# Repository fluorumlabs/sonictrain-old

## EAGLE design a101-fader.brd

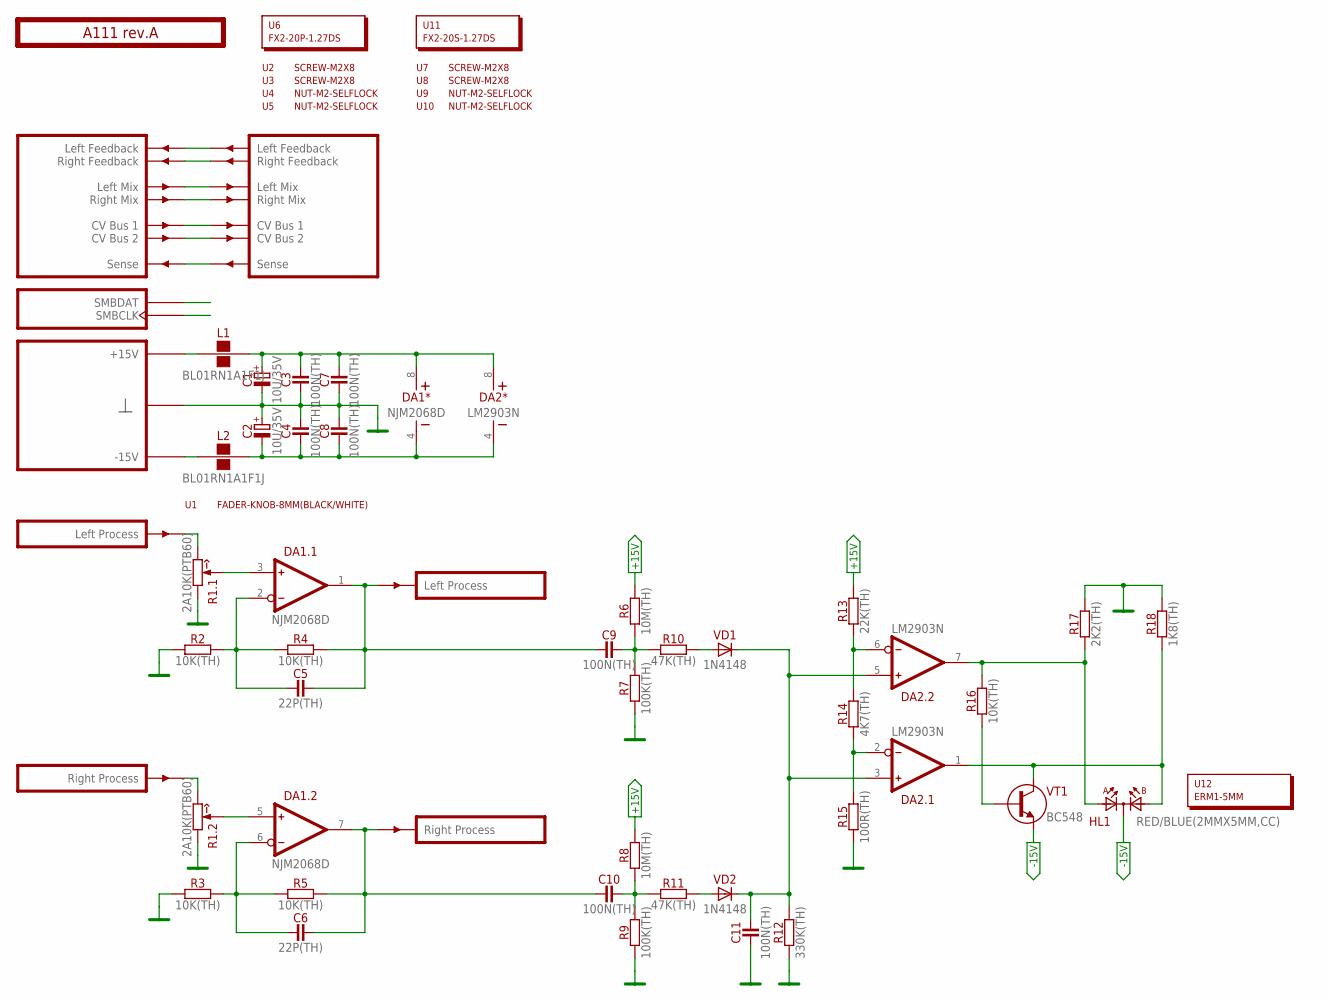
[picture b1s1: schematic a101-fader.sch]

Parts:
C1, C2: 10U/35V; E2-5
C3, C4, C7, C8, C9, C10, C11: 100N(TH); C050-024X044
C5, C6: 22P(TH); C050-024X044
DA1: NJM2068D; DIP-8
DA2: LM2903N; DIP-8
HL1: RED/BLUE(2MMX5MM,CC); LED2X5-3PIN
L1, L2: BL01RN1A1F1J; BL01RN1A
PCB1: A111 rev.A; ST2-BOARD-50
R1: 2A10K(PTB60); PTB6044
R2, R3, R4, R5, R16: 10K(TH); R-0207/10
R6, R8: 10M(TH); R-0207/10
R7, R9: 100K(TH); R-0207/10
R10, R11: 47K(TH); R-0207/10
R12: 330K(TH); R-0207/10
R13: 22K(TH); R-0207/10
R14: 4K7(TH); R-0207/10
R15: 100R(TH); R-0207/10
R17: 2K2(TH); R-0207/10
R18: 1K8(TH); R-0207/10
U1: FADER-KNOB-8MM(BLACK/WHITE); EMPTY
U2, U3, U7, U8: SCREW-M2X8; EMPTY
U4, U5, U9, U10: NUT-M2-SELFLOCK; EMPTY
U6: FX2-20P-1.27DS; EMPTY
U11: FX2-20S-1.27DS; EMPTY
U12: ERM1-5MM; EMPTY
VD1, VD2: 1N4148; DO35-7
VT1: BC548; TO92

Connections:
+15V: R6.2, R8.2, R13.2
-15V: HL1.K, VT1.3 (E)
GND: C1.-, C2.+, C3.1, C4.2, C7.1, C8.2, C11.1, PCB1.B4 (GND), PCB1.B4' (GND), PCB1.B5 (GND), PCB1.B5' (GND), PCB1.B6 (GND), PCB1.B6' (GND), PCB1.B7 (GND), PCB1.B7' (GND), PCB1.B8 (GND), PCB1.B8' (GND), R1.A1 (CCW), R1.B1 (CCW), R2.1, R3.1, R7.1, R9.1, R12.1, R15.1, R17.2, R18.2
unnamed: PCB1.ALFBK (LFBK), PCB1.ALFBK' (LFBK')
unnamed: PCB1.ARFBK (RFBK), PCB1.ARFBK' (RFBK')
unnamed: PCB1.ALMIX (LMIX), PCB1.ALMIX' (LMIX')
unnamed: PCB1.ARMIX (RMIX), PCB1.ARMIX' (RMIX')
unnamed: PCB1.ACV1 (CV1), PCB1.ACV1' (CV1')
unnamed: PCB1.ACV2 (CV2), PCB1.ACV2' (CV2')
unnamed: PCB1.BSENSE (SENSE), PCB1.BSENSE' (SENSE')
unnamed: PCB1.ASMBDAT (SMBDAT), PCB1.ASMBDAT' (SMBDAT)
unnamed: PCB1.ASMBCLK (SMBCLK), PCB1.ASMBCLK' (SMBCLK)
unnamed: PCB1.BINL (INL), R1.A3 (CW)
unnamed: DA1.3 (IN+), R1.A2 (W)
unnamed: C5.1, DA1.2 (IN-), R2.2, R4.1
unnamed: PCB1.BINR (INR), R1.B3 (CW)
unnamed: DA1.5 (IN+), R1.B2 (W)
unnamed: C6.1, DA1.6 (IN-), R3.2, R5.1
unnamed: C6.2, C10.1, DA1.7 (OUT), PCB1.BOUTR' (OUTR), R5.2
unnamed: C5.2, C9.1, DA1.1 (OUT), PCB1.BOUTL' (OUTL), R4.2
unnamed: C9.2, R6.1, R7.2, R10.1
unnamed: R10.2, VD1.A
unnamed: C10.2, R8.1, R9.2, R11.1
unnamed: R11.2, VD2.A
unnamed: C11.2, DA2.3 (IN+), DA2.5 (IN+), R12.2, VD1.C, VD2.C
unnamed: L1.1, PCB1.A+15 (P+15V), PCB1.A+15' (P+15V), PCB1.B+15 (P+15V), PCB1.B+15' (P+15V)
unnamed: DA2.2 (IN-), R14.1, R15.2
unnamed: DA2.6 (IN-), R13.1, R14.2
unnamed: DA2.1 (OUT), HL1.A2, R18.1, VT1.1 (C)
unnamed: C1.+, C3.2, C7.2, DA1.8 (V+), DA2.8 (V+), L1.2
unnamed: L2.1, PCB1.A-15 (P-15V), PCB1.A-15' (P-15V), PCB1.B-15 (P-15V), PCB1.B-15' (P-15V)
unnamed: C2.-, C4.1, C8.1, DA1.4 (V-), DA2.4 (V-), L2.2
unnamed: DA2.7 (OUT), HL1.A1, R16.2, R17.1
unnamed: R16.1, VT1.2 (B)

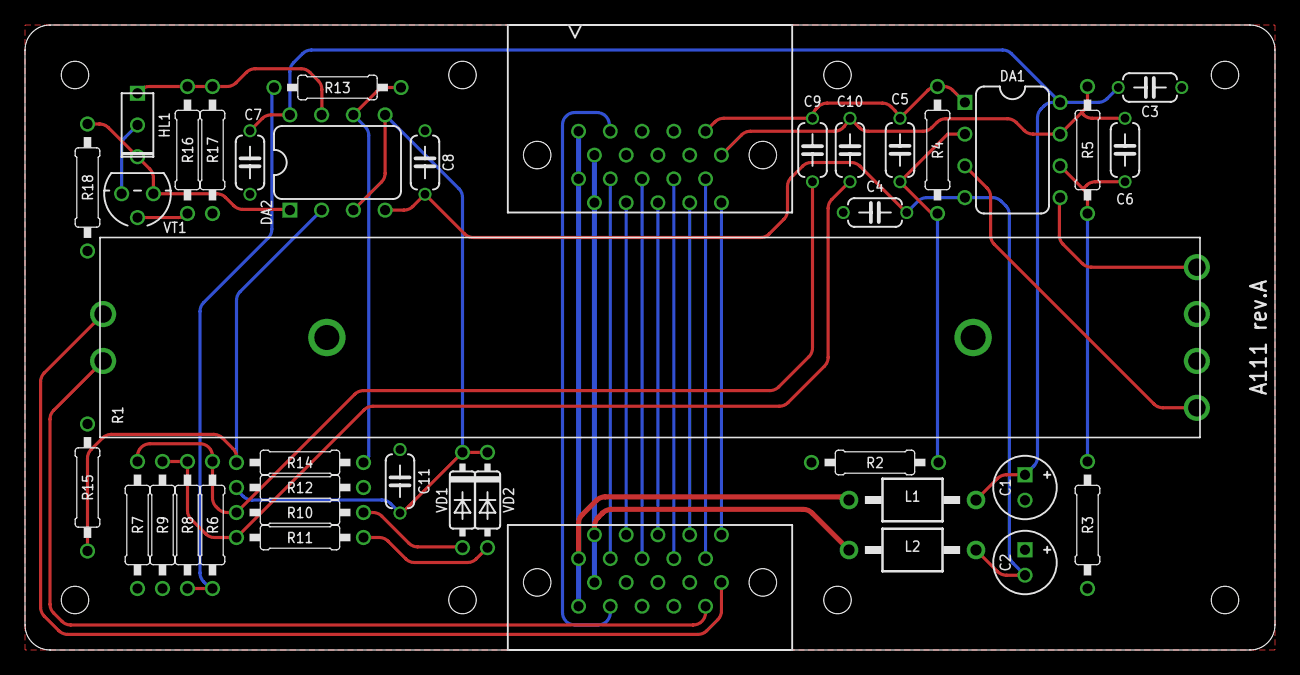
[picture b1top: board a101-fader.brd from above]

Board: 2 copper layers, 100.0 x 50.0 mm, 50 parts (0 on the bottom side), 34 nets.

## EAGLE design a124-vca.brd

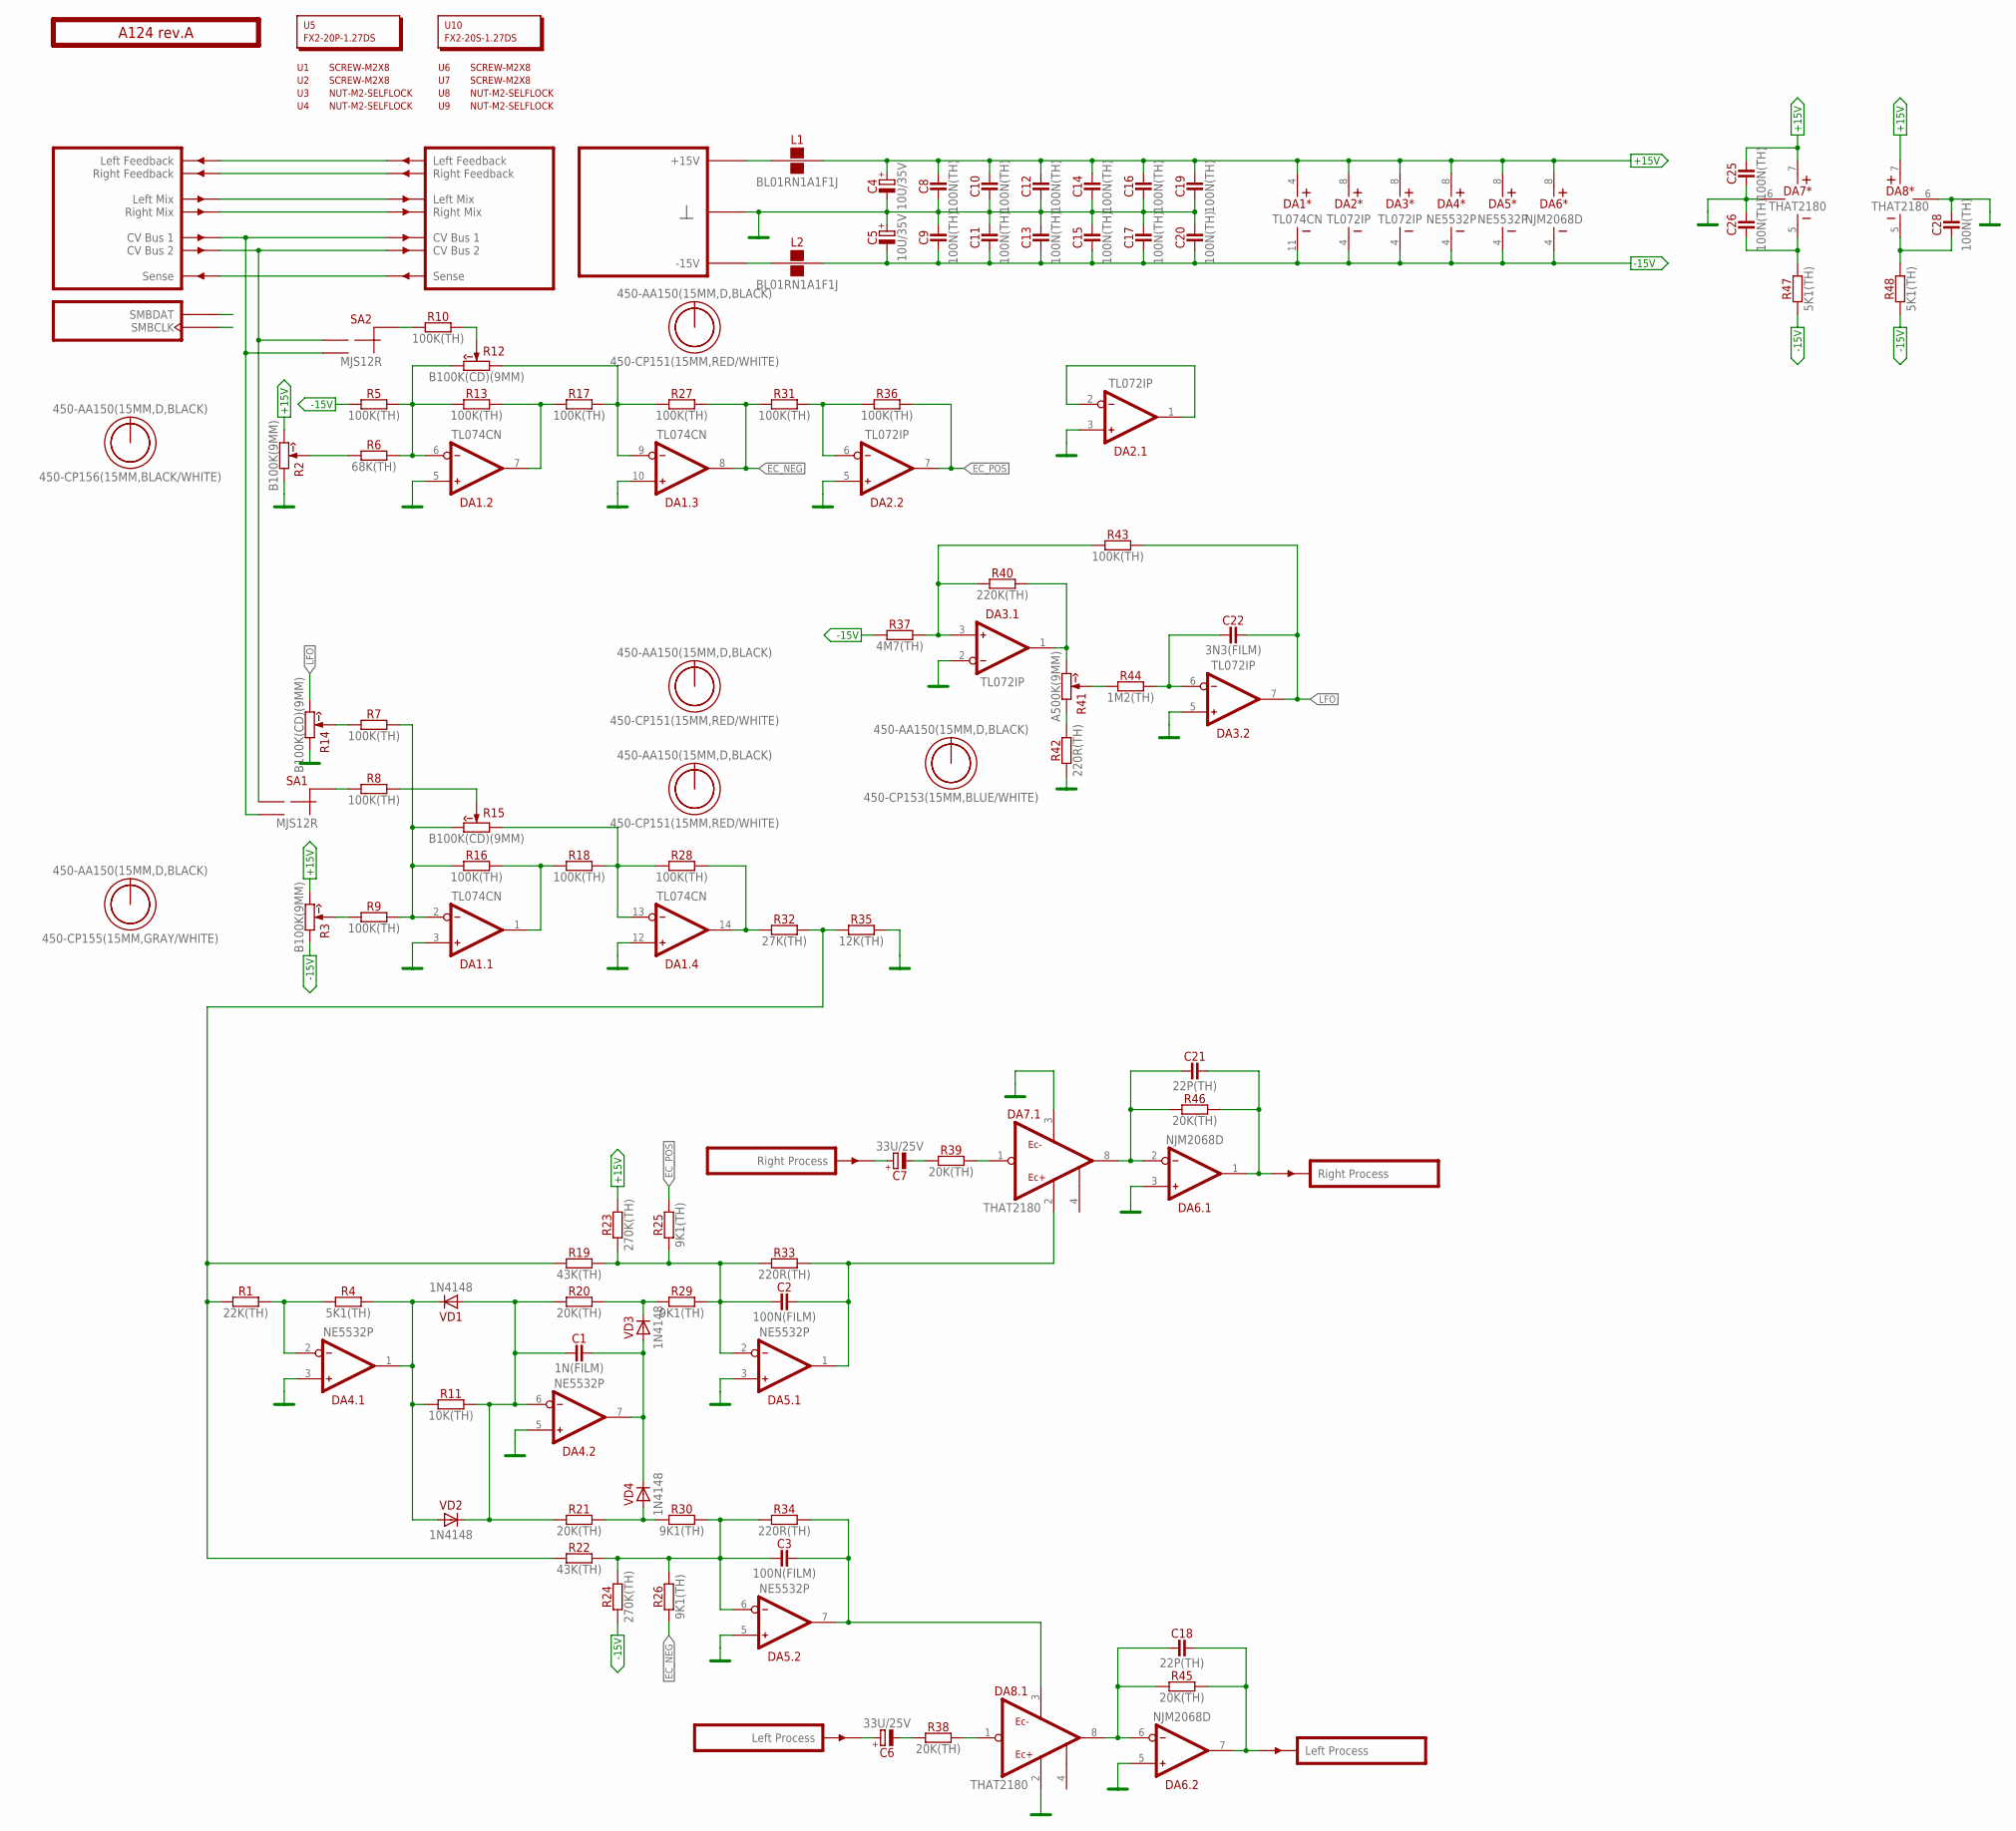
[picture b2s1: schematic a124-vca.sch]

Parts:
C1: 1N(FILM); C050-025X075
C2, C3: 100N(FILM); C050-025X075
C4, C5: 10U/35V; E2-5
C6, C7: 33U/25V; E2,5-7
C8, C9, C10, C11, C12, C13, C14, C15, C16, C17, C19, C20, C25, C26, C28: 100N(TH); C050-024X044
C18, C21: 22P(TH); C050-024X044
C22: 3N3(FILM); C050-025X075
DA1: TL074CN; DIP-14
DA2, DA3: TL072IP; DIP-8
DA4, DA5: NE5532P; DIP-8
DA6: NJM2068D; DIP-8
DA7, DA8: THAT2180; SIL8
L1, L2: BL01RN1A1F1J; BL01RN1A
O1, O3, O5, O7, O9, O11: 450-AA150(15MM,D,BLACK); EMPTY
O2: 450-CP156(15MM,BLACK/WHITE); EMPTY
O4: 450-CP155(15MM,GRAY/WHITE); EMPTY
O6, O8, O10: 450-CP151(15MM,RED/WHITE); EMPTY
O12: 450-CP153(15MM,BLUE/WHITE); EMPTY
PCB1: A124 rev.A; ST2-BOARD-74
R1: 22K(TH); R-0207/10
R2, R3: B100K(9MM); RV09-SINGLE
R4, R47, R48: 5K1(TH); R-0207/10
R5, R7, R8, R9, R10, R13, R16, R17, R18, R27, R28, R31, R36, R43: 100K(TH); R-0207/10
R6: 68K(TH); R-0207/10
R11: 10K(TH); R-0207/10
R12, R14, R15: B100K(CD)(9MM); RV09-SINGLE
R19, R22: 43K(TH); R-0207/10
R20, R21, R38, R39, R45, R46: 20K(TH); R-0207/10
R23, R24: 270K(TH); R-0207/10
R25, R26, R29, R30: 9K1(TH); R-0207/10
R32: 27K(TH); R-0207/10
R33, R34, R42: 220R(TH); R-0207/10
R35: 12K(TH); R-0207/10
R37: 4M7(TH); R-0207/10
R40: 220K(TH); R-0207/10
R41: A500K(9MM); RV09-SINGLE
R44: 1M2(TH); R-0207/10
SA1, SA2: MJS12R; APEM-MJS12R
U1, U2, U6, U7: SCREW-M2X8; EMPTY
U3, U4, U8, U9: NUT-M2-SELFLOCK; EMPTY
U5: FX2-20P-1.27DS; EMPTY
U10: FX2-20S-1.27DS; EMPTY
VD1, VD2, VD3, VD4: 1N4148; DO35-7

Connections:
+15V: C4.+, C8.2, C10.2, C12.2, C14.2, C16.2, C19.2, C25.2, DA1.4 (V+), DA2.8 (V+), DA3.8 (V+), DA4.8 (V+), DA5.8 (V+), DA6.8 (V+), DA7.7 (V+), DA8.7 (V+), L1.2, R2.3 (CW), R3.3 (CW), R23.2
-15V: C5.-, C9.1, C11.1, C13.1, C15.1, C17.1, C20.1, DA1.11 (V-), DA2.4 (V-), DA3.4 (V-), DA4.4 (V-), DA5.4 (V-), DA6.4 (V-), L2.2, R3.1 (CCW), R5.1, R24.1, R37.1, R47.1, R48.1
EC_NEG: DA1.8 (OUT), R26.1, R27.2, R31.1
EC_POS: DA2.7 (OUT), R25.2, R36.2
GND: C4.-, C5.+, C8.1, C9.2, C10.1, C11.2, C12.1, C13.2, C14.1, C15.2, C16.1, C17.2, C19.1, C20.2, C25.1, C26.2, C28.2, DA1.3 (IN+), DA1.5 (IN+), DA1.10 (IN+), DA1.12 (IN+), DA2.3 (IN+), DA2.5 (IN+), DA3.2 (IN-), DA3.5 (IN+), DA4.3 (IN+), DA4.5 (IN+), DA5.3 (IN+), DA5.5 (IN+), DA6.3 (IN+), DA6.5 (IN+), DA7.3 (EC-), DA7.6 (GND), DA8.2 (EC+), DA8.6 (GND), PCB1.B4 (GND), PCB1.B4' (GND), PCB1.B5 (GND), PCB1.B5' (GND), PCB1.B6 (GND), PCB1.B6' (GND), PCB1.B7 (GND), PCB1.B7' (GND), PCB1.B8 (GND), PCB1.B8' (GND), R2.1 (CCW), R14.1 (CCW), R35.2, R42.1
LFO: C22.2, DA3.7 (OUT), R14.3 (CW), R43.2
LMIX: PCB1.ALMIX (LMIX), PCB1.ALMIX' (LMIX')
unnamed: L1.1, PCB1.A+15 (P+15V), PCB1.A+15' (P+15V), PCB1.B+15 (P+15V), PCB1.B+15' (P+15V)
unnamed: PCB1.ALFBK (LFBK), PCB1.ALFBK' (LFBK')
unnamed: R10.2, R12.2 (W)
unnamed: PCB1.ARFBK (RFBK), PCB1.ARFBK' (RFBK')
unnamed: DA1.6 (IN-), R5.2, R6.2, R12.3 (CW), R13.1
unnamed: DA1.7 (OUT), R13.2, R17.1
unnamed: DA1.9 (IN-), R12.1 (CCW), R17.2, R27.1
unnamed: DA4.2 (IN-), R1.2, R4.1
unnamed: R10.1, SA2.C (CM)
unnamed: R8.2, R15.2 (W)
unnamed: DA1.2 (IN-), R7.2, R9.2, R15.3 (CW), R16.1
unnamed: DA1.1 (OUT), R16.2, R18.1
unnamed: R2.2 (W), R6.1
unnamed: DA1.13 (IN-), R15.1 (CCW), R18.2, R28.1
unnamed: DA4.1 (OUT), R4.2, R11.1, VD1.C, VD2.A
unnamed: PCB1.BSENSE (SENSE), PCB1.BSENSE' (SENSE')
unnamed: R8.1, SA1.C (CM)
unnamed: PCB1.ACV1 (CV1), PCB1.ACV1' (CV1'), SA1.NO (2), SA2.NO (2)
unnamed: R3.2 (W), R9.1
unnamed: DA1.14 (OUT), R28.2, R32.1
unnamed: DA2.6 (IN-), R31.2, R36.1
unnamed: C1.2, DA4.7 (OUT), VD3.A, VD4.C
unnamed: R20.2, R29.1, VD3.C
unnamed: C1.1, DA4.6 (IN-), R11.2, R20.1, R21.1, VD1.A, VD2.C
unnamed: L2.1, PCB1.A-15 (P-15V), PCB1.A-15' (P-15V), PCB1.B-15 (P-15V), PCB1.B-15' (P-15V)
unnamed: R21.2, R30.1, VD4.A
unnamed: C2.2, DA5.1 (OUT), DA7.2 (EC+), R33.2
unnamed: DA3.1 (OUT), R40.2, R41.3 (CW)
unnamed: R41.1 (CCW), R42.2
unnamed: C3.2, DA5.7 (OUT), DA8.3 (EC-), R34.2
unnamed: C3.1, DA5.6 (IN-), R22.2, R24.2, R26.2, R30.2, R34.1
unnamed: C2.1, DA5.2 (IN-), R19.2, R23.1, R25.1, R29.2, R33.1
unnamed: R41.2 (W), R44.1
unnamed: C22.1, DA3.6 (IN-), R44.2
unnamed: C26.1, DA7.5 (V-), R47.2
unnamed: R7.1, R14.2 (W)
unnamed: C28.1, DA8.5 (V-), R48.2
unnamed: PCB1.ASMBDAT (SMBDAT), PCB1.ASMBDAT' (SMBDAT)
unnamed: DA3.3 (IN+), R37.2, R40.1, R43.1
unnamed: DA2.1 (OUT), DA2.2 (IN-)
unnamed: C18.1, DA6.6 (IN-), DA8.8 (OUT), R45.1
unnamed: PCB1.ACV2 (CV2), PCB1.ACV2' (CV2'), SA1.NC (1), SA2.NC (1)
unnamed: PCB1.ASMBCLK (SMBCLK), PCB1.ASMBCLK' (SMBCLK)
unnamed: C18.2, DA6.7 (OUT), PCB1.BOUTL' (OUTL), R45.2
unnamed: C21.1, DA6.2 (IN-), DA7.8 (OUT), R46.1
unnamed: C21.2, DA6.1 (OUT), PCB1.BOUTR' (OUTR), R46.2
unnamed: C6.-, R38.1
unnamed: DA8.1 (IN-), R38.2
unnamed: DA7.1 (IN-), R39.2
unnamed: C7.-, R39.1
unnamed: C7.+, PCB1.BINR (INR)
unnamed: C6.+, PCB1.BINL (INL)
unnamed: R1.1, R19.1, R22.1, R32.2, R35.1
RMIX: PCB1.ARMIX (RMIX), PCB1.ARMIX' (RMIX')

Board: 2 copper layers, 112 parts (0 on the bottom side), 61 nets, no tracks yet.

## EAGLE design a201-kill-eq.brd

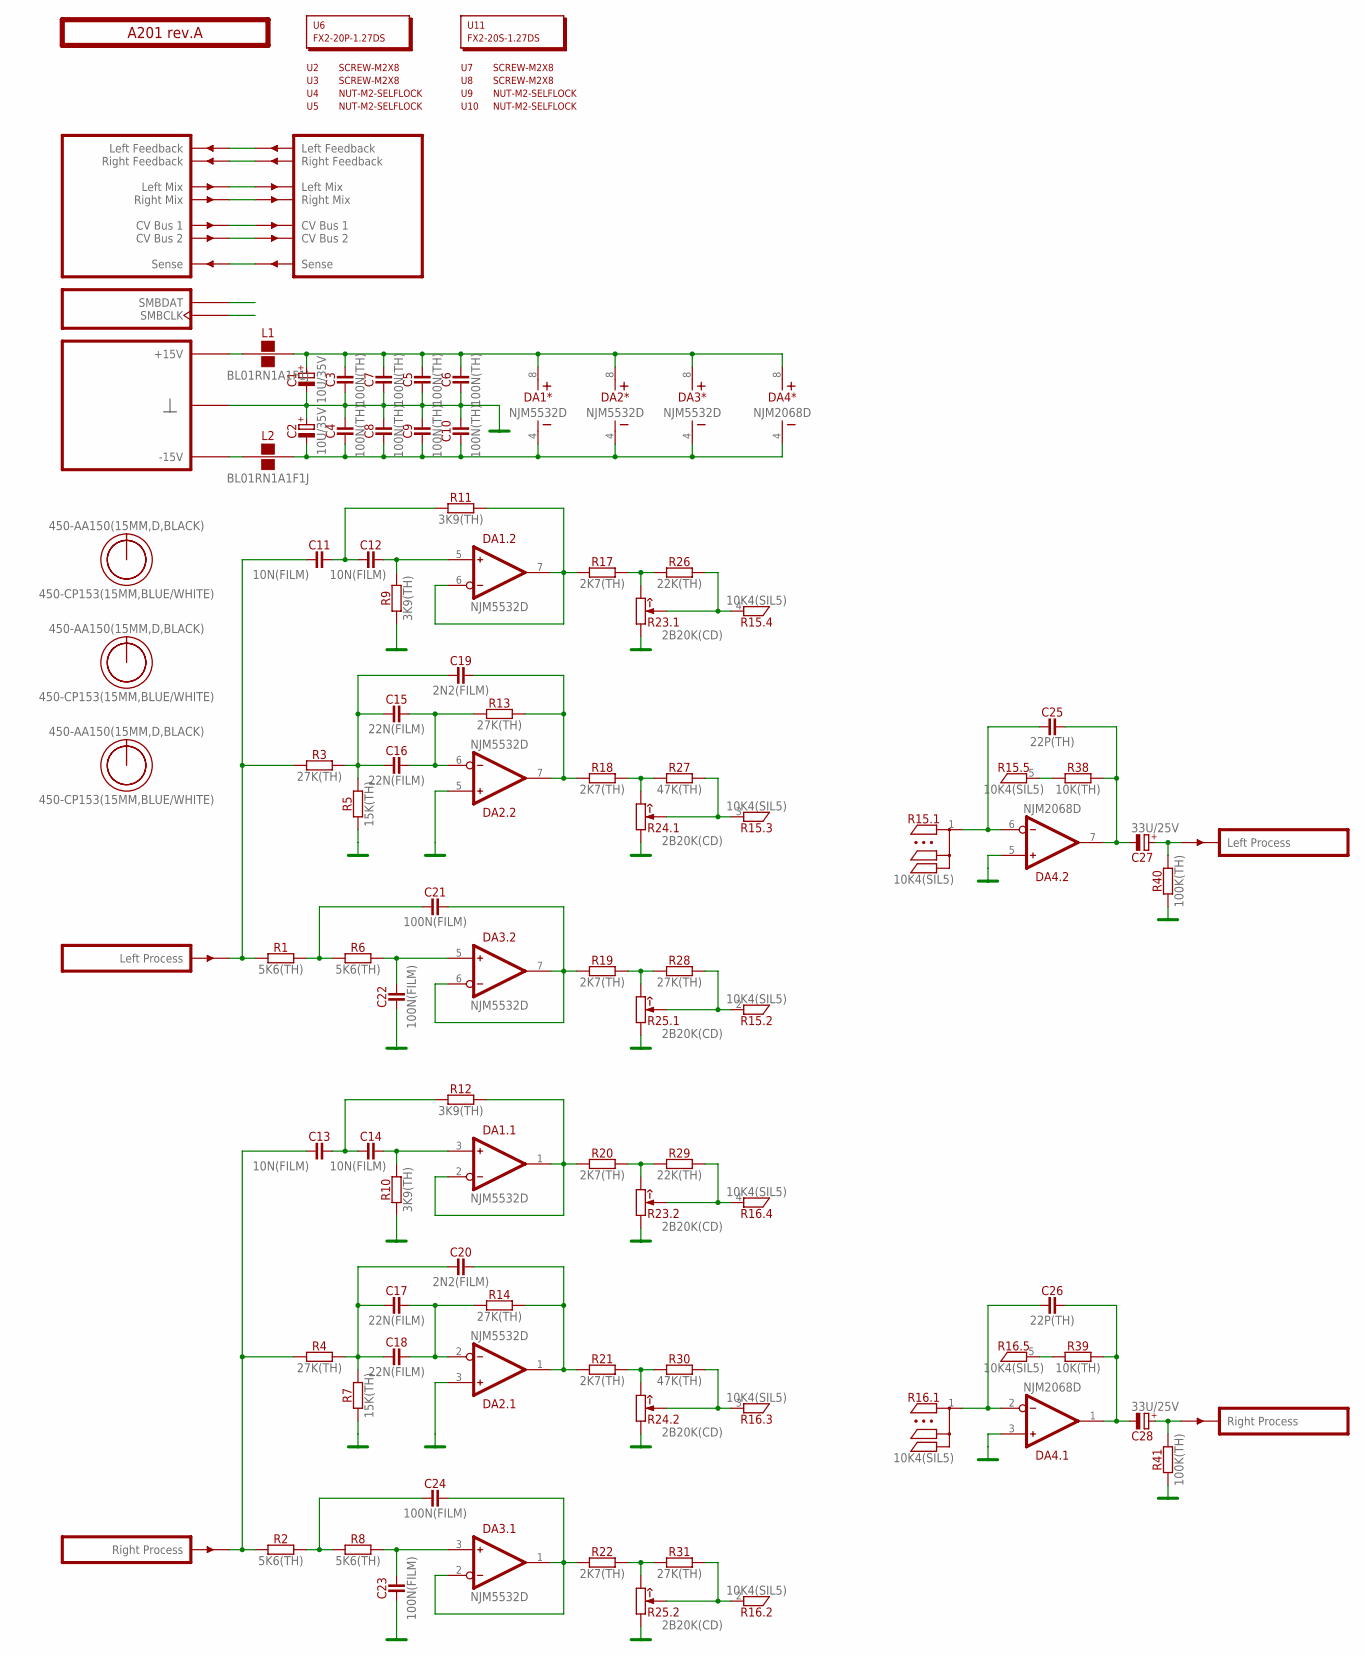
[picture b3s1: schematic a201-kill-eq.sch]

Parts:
C1, C2: 10U/35V; E2-5
C3, C4, C5, C6, C7, C8, C9, C10: 100N(TH); C050-024X044
C11, C12, C13, C14: 10N(FILM); C050-025X075
C15, C16, C17, C18: 22N(FILM); C050-025X075
C19, C20: 2N2(FILM); C050-025X075
C21, C22, C23, C24: 100N(FILM); C050-025X075
C25, C26: 22P(TH); C050-024X044
C27, C28: 33U/25V; E2,5-7
DA1, DA2, DA3: NJM5532D; DIP-8
DA4: NJM2068D; DIP-8
L1, L2: BL01RN1A1F1J; BL01RN1A
O1, O2, O3: 450-AA150(15MM,D,BLACK); EMPTY
O4, O5, O6: 450-CP153(15MM,BLUE/WHITE); EMPTY
PCB1: A201 rev.A; ST2-BOARD-50
R1, R2, R6, R8: 5K6(TH); R-0207/10
R3, R4, R13, R14, R28, R31: 27K(TH); R-0207/10
R5, R7: 15K(TH); R-0207/10
R9, R10, R11, R12: 3K9(TH); R-0207/10
R15, R16: 10K4(SIL5); R-SIL5
R17, R18, R19, R20, R21, R22: 2K7(TH); R-0207/10
R23, R24, R25: 2B20K(CD); RV11-DUAL
R26, R29: 22K(TH); R-0207/10
R27, R30: 47K(TH); R-0207/10
R38, R39: 10K(TH); R-0207/10
R40, R41: 100K(TH); R-0207/10
U2, U3, U7, U8: SCREW-M2X8; EMPTY
U4, U5, U9, U10: NUT-M2-SELFLOCK; EMPTY
U6: FX2-20P-1.27DS; EMPTY
U11: FX2-20S-1.27DS; EMPTY

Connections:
GND: C1.-, C2.+, C3.1, C4.2, C5.1, C6.1, C7.1, C8.2, C9.2, C10.2, C22.1, C23.1, DA2.3 (IN+), DA2.5 (IN+), DA4.3 (IN+), DA4.5 (IN+), PCB1.B4 (GND), PCB1.B4' (GND), PCB1.B5 (GND), PCB1.B5' (GND), PCB1.B6 (GND), PCB1.B6' (GND), PCB1.B7 (GND), PCB1.B7' (GND), PCB1.B8 (GND), PCB1.B8' (GND), R5.1, R7.1, R9.1, R10.1, R23.1 (CCW), R23.1' (CCW), R24.1 (CCW), R24.1' (CCW), R25.1 (CCW), R25.1' (CCW), R40.1, R41.1
LIO: C11.1, PCB1.BINL (INL), R1.1, R3.1
LIO': C27.+, PCB1.BOUTL' (OUTL), R40.2
unnamed: PCB1.ALFBK (LFBK), PCB1.ALFBK' (LFBK')
unnamed: PCB1.ARFBK (RFBK), PCB1.ARFBK' (RFBK')
unnamed: PCB1.ALMIX (LMIX), PCB1.ALMIX' (LMIX')
unnamed: PCB1.ARMIX (RMIX), PCB1.ARMIX' (RMIX')
unnamed: PCB1.ACV1 (CV1), PCB1.ACV1' (CV1')
unnamed: PCB1.ACV2 (CV2), PCB1.ACV2' (CV2')
unnamed: PCB1.BSENSE (SENSE), PCB1.BSENSE' (SENSE')
unnamed: PCB1.ASMBDAT (SMBDAT), PCB1.ASMBDAT' (SMBDAT)
unnamed: PCB1.ASMBCLK (SMBCLK), PCB1.ASMBCLK' (SMBCLK)
unnamed: C11.2, C12.1, R11.1
unnamed: C12.2, DA1.5 (IN+), R9.2
unnamed: DA1.6 (IN-), DA1.7 (OUT), R11.2, R17.1
unnamed: R17.2, R23.3 (CW), R26.1
unnamed: R15.4, R23.2 (W), R26.2
unnamed: C15.1, C16.1, C19.1, R3.2, R5.2
unnamed: C15.2, C16.2, DA2.6 (IN-), R13.1
unnamed: C19.2, DA2.7 (OUT), R13.2, R18.1
unnamed: R18.2, R24.3 (CW), R27.1
unnamed: R15.3, R24.2 (W), R27.2
unnamed: C21.1, R1.2, R6.1
unnamed: C22.2, DA3.5 (IN+), R6.2
unnamed: C21.2, DA3.6 (IN-), DA3.7 (OUT), R19.1
unnamed: R19.2, R25.3 (CW), R28.1
unnamed: R15.2, R25.2 (W), R28.2
unnamed: L1.1, PCB1.A+15 (P+15V), PCB1.A+15' (P+15V), PCB1.B+15 (P+15V), PCB1.B+15' (P+15V)
unnamed: R16.5, R39.1
unnamed: C13.2, C14.1, R12.1
unnamed: C14.2, DA1.3 (IN+), R10.2
unnamed: DA1.1 (OUT), DA1.2 (IN-), R12.2, R20.1
unnamed: R20.2, R23.3' (CW), R29.1
unnamed: R16.4, R23.2' (W), R29.2
unnamed: R15.5, R38.1
unnamed: C17.1, C18.1, C20.1, R4.2, R7.2
unnamed: C17.2, C18.2, DA2.2 (IN-), R14.1
unnamed: C20.2, DA2.1 (OUT), R14.2, R21.1
unnamed: R21.2, R24.3' (CW), R30.1
unnamed: R16.3, R24.2' (W), R30.2
unnamed: C25.2, C27.-, DA4.7 (OUT), R38.2
unnamed: C24.1, R2.2, R8.1
unnamed: C23.2, DA3.3 (IN+), R8.2
unnamed: C24.2, DA3.1 (OUT), DA3.2 (IN-), R22.1
unnamed: R22.2, R25.3' (CW), R31.1
unnamed: R16.2, R25.2' (W), R31.2
unnamed: C26.2, C28.-, DA4.1 (OUT), R39.2
unnamed: C1.+, C3.2, C5.2, C6.2, C7.2, DA1.8 (V+), DA2.8 (V+), DA3.8 (V+), DA4.8 (V+), L1.2
unnamed: L2.1, PCB1.A-15 (P-15V), PCB1.A-15' (P-15V), PCB1.B-15 (P-15V), PCB1.B-15' (P-15V)
unnamed: C2.-, C4.1, C8.1, C9.1, C10.1, DA1.4 (V-), DA2.4 (V-), DA3.4 (V-), DA4.4 (V-), L2.2
unnamed: C28.+, PCB1.BOUTR' (OUTR), R41.2
unnamed: C25.1, DA4.6 (IN-), R15.1
unnamed: C26.1, DA4.2 (IN-), R16.1
RIO: C13.1, PCB1.BINR (INR), R2.1, R4.1

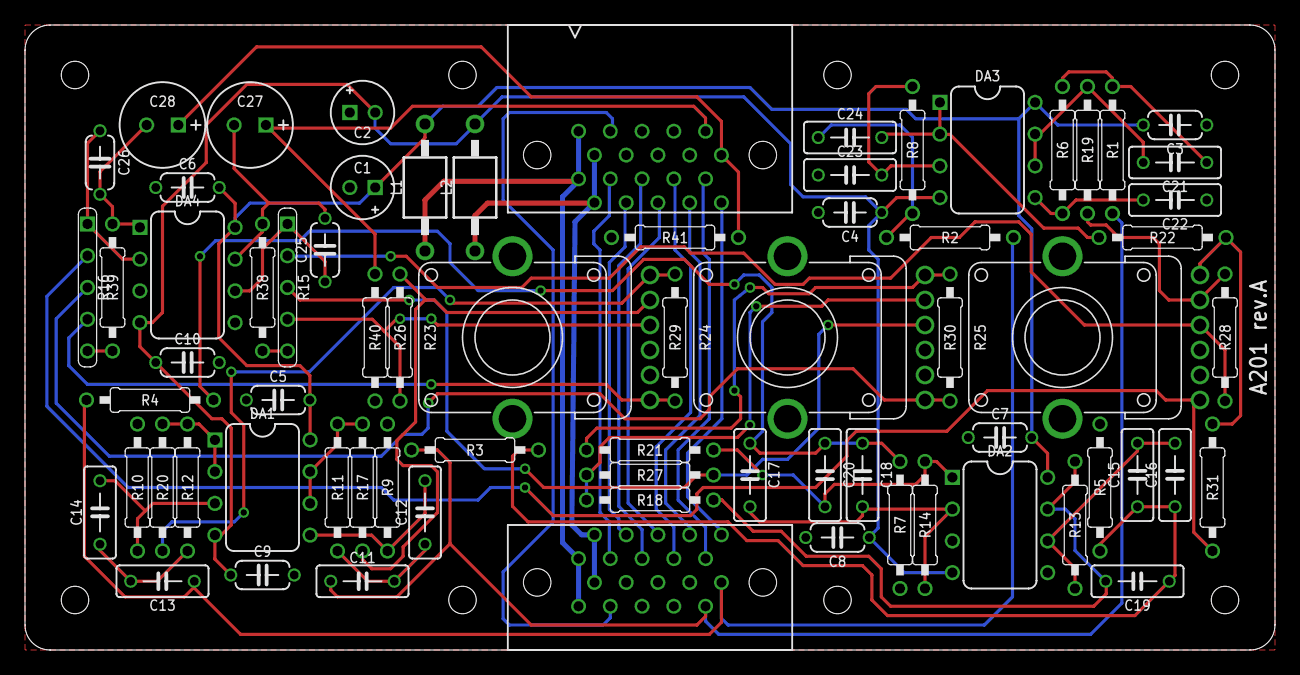
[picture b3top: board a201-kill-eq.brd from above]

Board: 2 copper layers, 100.0 x 50.0 mm, 86 parts (0 on the bottom side), 54 nets.

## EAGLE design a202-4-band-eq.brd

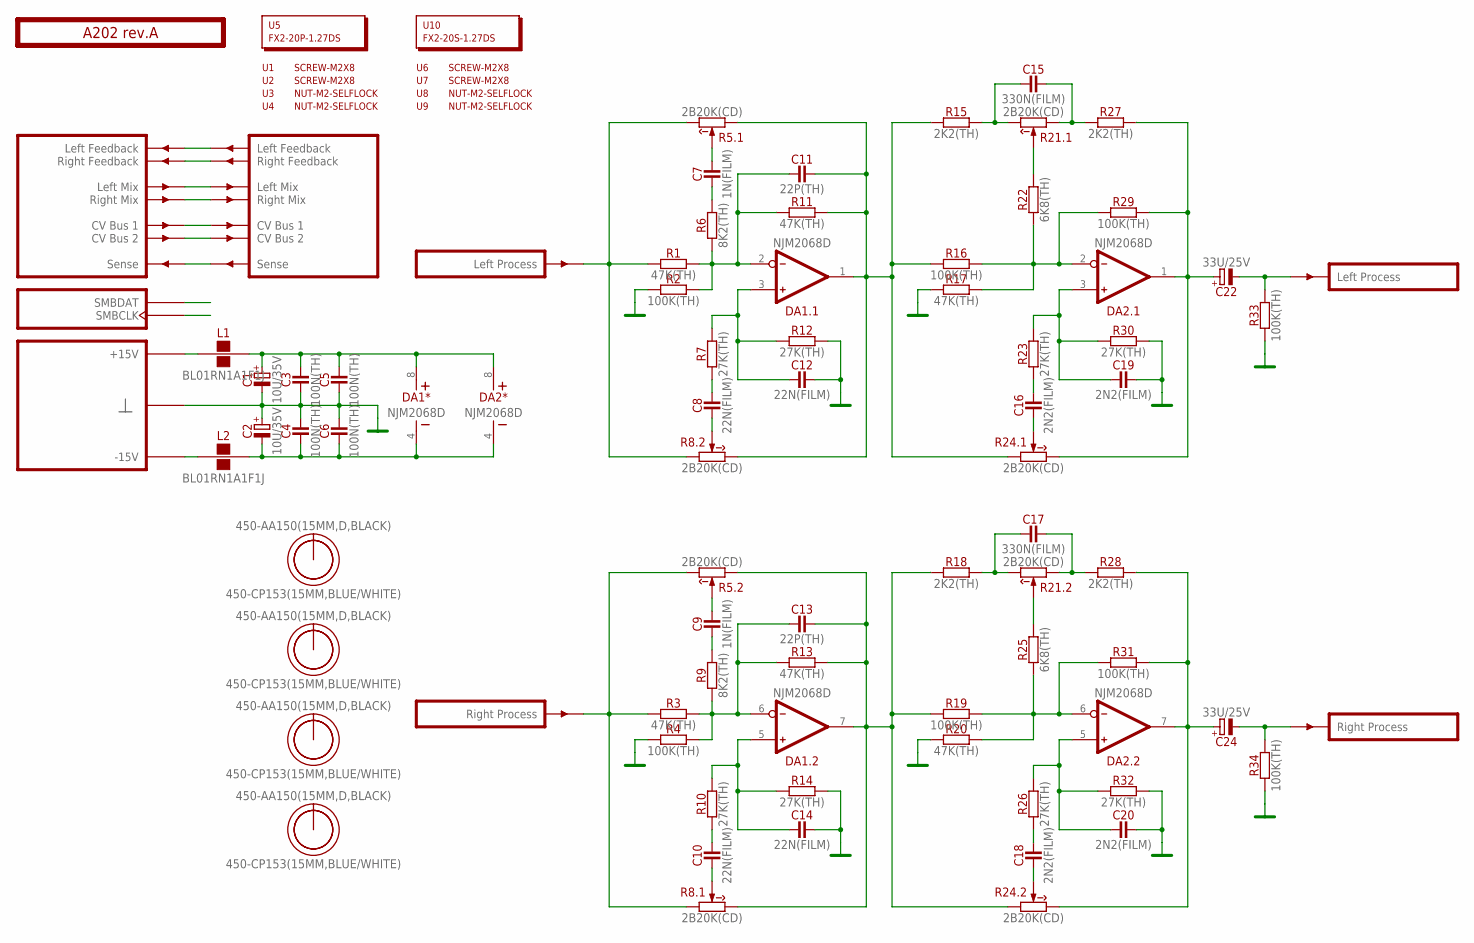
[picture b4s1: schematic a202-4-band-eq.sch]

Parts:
C1, C2: 10U/35V; E2-5
C3, C4, C5, C6: 100N(TH); C050-024X044
C7, C9: 1N(FILM); C050-025X075
C8, C10, C12, C14: 22N(FILM); C050-025X075
C11, C13: 22P(TH); C050-024X044
C15, C17: 330N(FILM); C050-035X075
C16, C18, C19, C20: 2N2(FILM); C050-025X075
C22, C24: 33U/25V; E2,5-7
DA1, DA2: NJM2068D; DIP-8
L1, L2: BL01RN1A1F1J; BL01RN1A
O1, O2, O3, O4: 450-AA150(15MM,D,BLACK); EMPTY
O5, O6, O7, O8: 450-CP153(15MM,BLUE/WHITE); EMPTY
PCB1: A202 rev.A; ST2-BOARD-50
R1, R3, R11, R13, R17, R20: 47K(TH); R-0207/10
R2, R4, R16, R19, R29, R31, R33, R34: 100K(TH); R-0207/10
R5, R8, R21, R24: 2B20K(CD); RV11-DUAL
R6, R9: 8K2(TH); R-0207/10
R7, R10, R12, R14, R23, R26, R30, R32: 27K(TH); R-0207/10
R15, R18, R27, R28: 2K2(TH); R-0207/10
R22, R25: 6K8(TH); R-0207/10
U1, U2, U6, U7: SCREW-M2X8; EMPTY
U3, U4, U8, U9: NUT-M2-SELFLOCK; EMPTY
U5: FX2-20P-1.27DS; EMPTY
U10: FX2-20S-1.27DS; EMPTY

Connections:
GND: C1.-, C2.+, C3.1, C4.2, C5.1, C6.2, C12.2, C14.2, C19.2, C20.2, PCB1.B4 (GND), PCB1.B4' (GND), PCB1.B5 (GND), PCB1.B5' (GND), PCB1.B6 (GND), PCB1.B6' (GND), PCB1.B7 (GND), PCB1.B7' (GND), PCB1.B8 (GND), PCB1.B8' (GND), R2.1, R4.1, R12.2, R14.2, R17.1, R20.1, R30.2, R32.2, R33.1, R34.1
unnamed: PCB1.ALFBK (LFBK), PCB1.ALFBK' (LFBK')
unnamed: PCB1.ARFBK (RFBK), PCB1.ARFBK' (RFBK')
unnamed: PCB1.ALMIX (LMIX), PCB1.ALMIX' (LMIX')
unnamed: PCB1.ARMIX (RMIX), PCB1.ARMIX' (RMIX')
unnamed: PCB1.ACV1 (CV1), PCB1.ACV1' (CV1')
unnamed: PCB1.ACV2 (CV2), PCB1.ACV2' (CV2')
unnamed: PCB1.BSENSE (SENSE), PCB1.BSENSE' (SENSE')
unnamed: PCB1.ASMBDAT (SMBDAT), PCB1.ASMBDAT' (SMBDAT)
unnamed: PCB1.ASMBCLK (SMBCLK), PCB1.ASMBCLK' (SMBCLK)
unnamed: C11.1, DA1.2 (IN-), R1.2, R2.2, R6.1, R11.1
unnamed: C11.2, DA1.1 (OUT), R5.1 (CCW), R8.3' (CW), R11.2, R15.1, R16.1, R24.1 (CCW)
unnamed: C7.1, R6.2
unnamed: C7.2, R5.2 (W)
unnamed: PCB1.BINL (INL), R1.1, R5.3 (CW), R8.1' (CCW)
unnamed: C12.1, DA1.3 (IN+), R7.2, R12.1
unnamed: DA2.2 (IN-), R16.2, R17.2, R22.1, R29.1
unnamed: C8.2, R7.1
unnamed: C8.1, R8.2' (W)
unnamed: C22.+, DA2.1 (OUT), R24.3 (CW), R27.2, R29.2
unnamed: C19.1, DA2.3 (IN+), R23.2, R30.1
unnamed: C16.2, R23.1
unnamed: C16.1, R24.2 (W)
unnamed: C15.2, R21.1 (CCW), R27.1
unnamed: C15.1, R15.2, R21.3 (CW)
unnamed: L1.1, PCB1.A+15 (P+15V), PCB1.A+15' (P+15V), PCB1.B+15 (P+15V), PCB1.B+15' (P+15V)
unnamed: R21.2 (W), R22.2
unnamed: C22.-, PCB1.BOUTL' (OUTL), R33.2
unnamed: C13.1, DA1.6 (IN-), R3.2, R4.2, R9.1, R13.1
unnamed: C13.2, DA1.7 (OUT), R5.1' (CCW), R8.3 (CW), R13.2, R18.1, R19.1, R24.1' (CCW)
unnamed: C9.1, R9.2
unnamed: C9.2, R5.2' (W)
unnamed: PCB1.BINR (INR), R3.1, R5.3' (CW), R8.1 (CCW)
unnamed: C14.1, DA1.5 (IN+), R10.2, R14.1
unnamed: C10.2, R10.1
unnamed: C10.1, R8.2 (W)
unnamed: DA2.6 (IN-), R19.2, R20.2, R25.1, R31.1
unnamed: C24.+, DA2.7 (OUT), R24.3' (CW), R28.2, R31.2
unnamed: C20.1, DA2.5 (IN+), R26.2, R32.1
unnamed: C18.2, R26.1
unnamed: C18.1, R24.2' (W)
unnamed: C17.2, R21.1' (CCW), R28.1
unnamed: C17.1, R18.2, R21.3' (CW)
unnamed: R21.2' (W), R25.2
unnamed: C24.-, PCB1.BOUTR' (OUTR), R34.2
unnamed: C1.+, C3.2, C5.2, DA1.8 (V+), DA2.8 (V+), L1.2
unnamed: L2.1, PCB1.A-15 (P-15V), PCB1.A-15' (P-15V), PCB1.B-15 (P-15V), PCB1.B-15' (P-15V)
unnamed: C2.-, C4.1, C6.1, DA1.4 (V-), DA2.4 (V-), L2.2

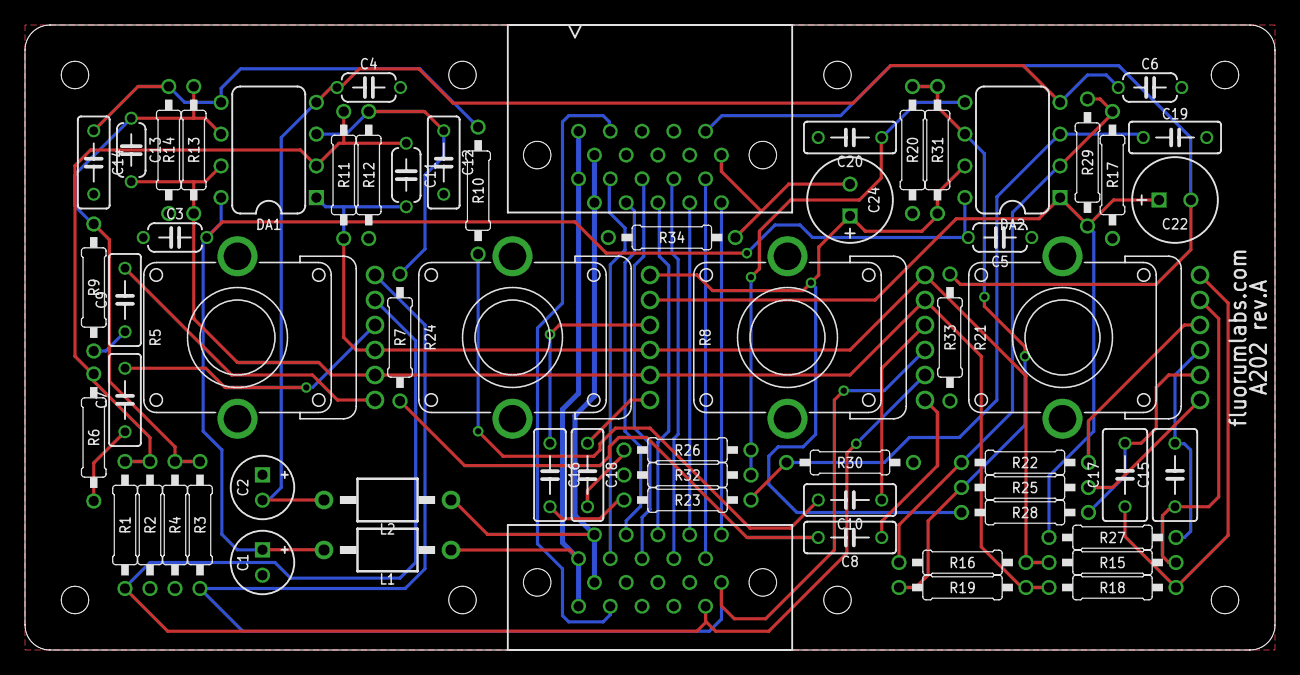
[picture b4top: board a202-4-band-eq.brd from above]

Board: 2 copper layers, 100.0 x 50.0 mm, 79 parts (0 on the bottom side), 48 nets.

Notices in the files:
parts and their libraries:
text: Copyright (c) 2015 fluorumlabs.com
CERN Open Hardware License v1.2
